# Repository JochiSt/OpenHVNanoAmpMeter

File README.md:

# OpenHVNanoAmpMeter
 Measure Nano Ampere at a high voltage supply

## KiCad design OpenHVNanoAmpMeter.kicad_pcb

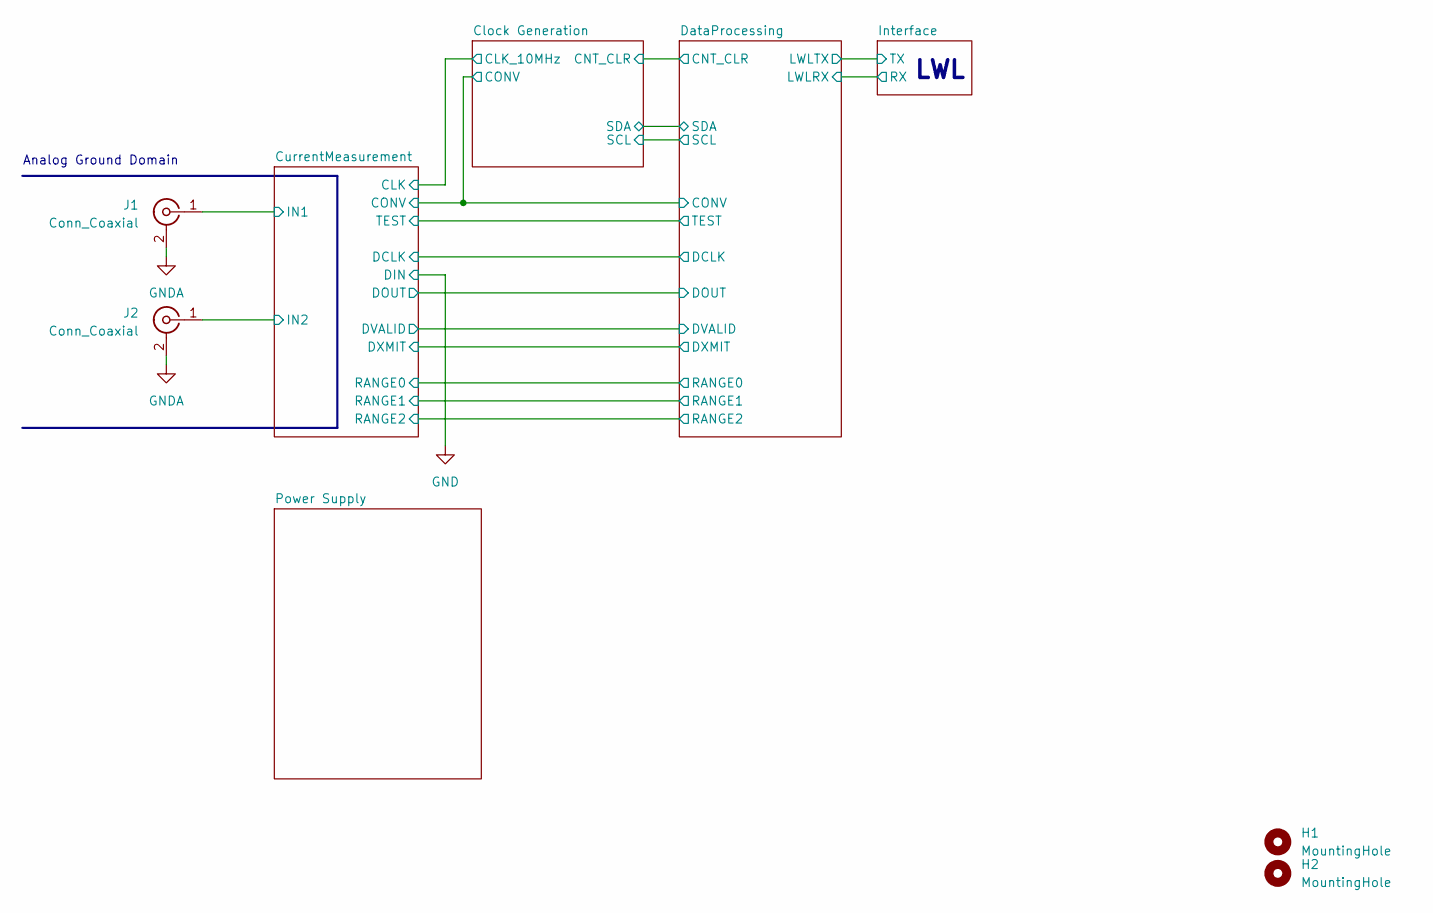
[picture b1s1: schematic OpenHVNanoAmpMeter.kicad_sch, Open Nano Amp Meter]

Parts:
H1, H2: MountingHole; MountingHole_3.2mm_M3_DIN965
J1, J2: Conn_Coaxial; SMA_Amphenol_132289_EdgeMount

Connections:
/CurrentMeasurement/IN1: J1.1 (In); also elsewhere on the board
/CurrentMeasurement/IN2: J2.1 (In); also elsewhere on the board
GNDA: J1.2 (Ext), J2.2 (Ext); also elsewhere on the board

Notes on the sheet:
LWL
Analog Ground Domain

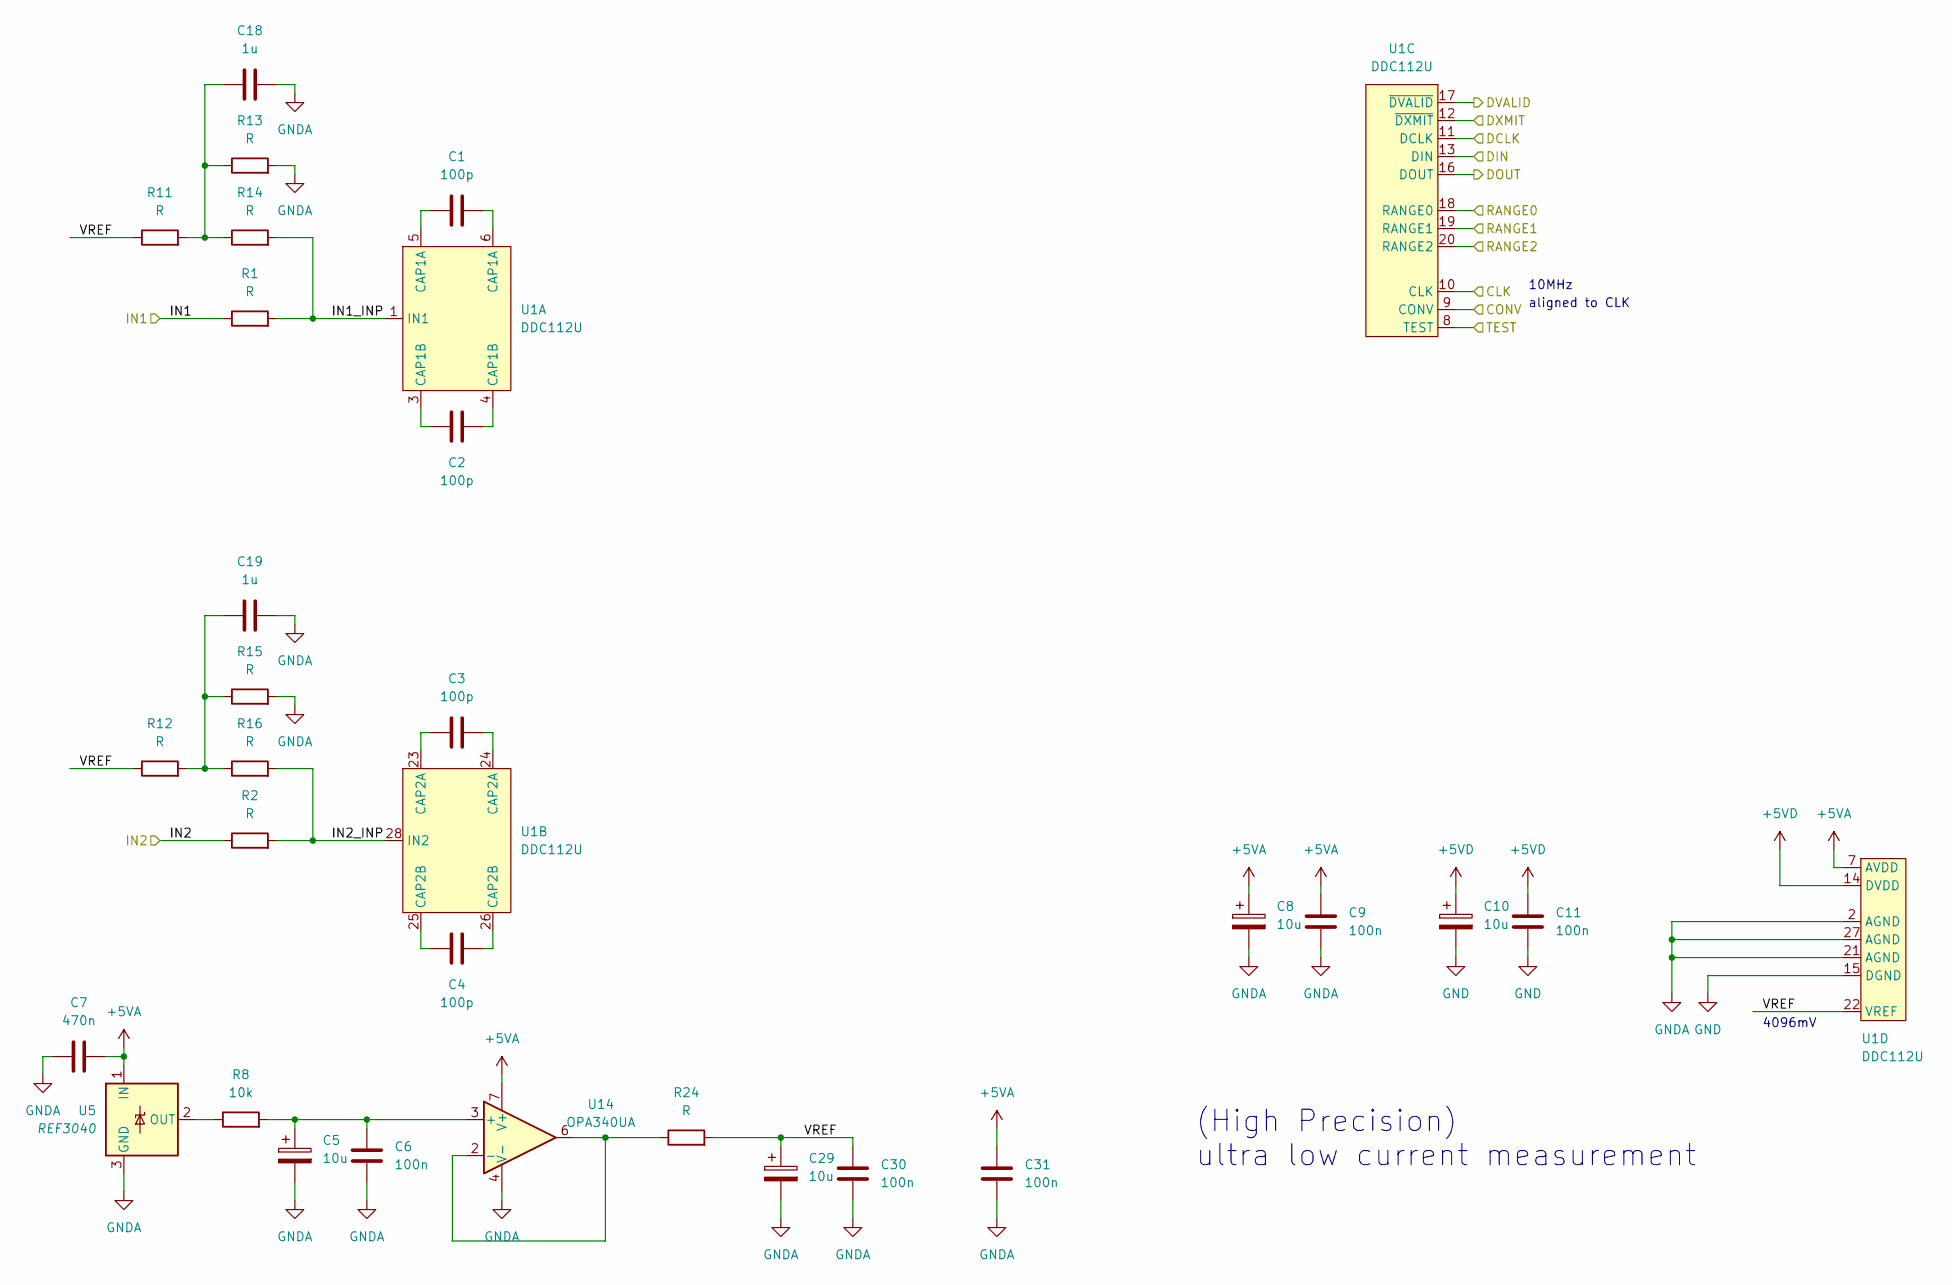
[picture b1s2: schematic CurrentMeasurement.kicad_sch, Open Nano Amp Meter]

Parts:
C1, C2, C3, C4: 100p; C_0402_1005Metric_Pad0.74x0.62mm_HandSolder
C5, C8, C10, C29: 10u; CP_Elec_4x3.9
C6, C9, C11, C30, C31: 100n; C_0603_1608Metric
C7: 470n; C_0603_1608Metric
C18, C19: 1u; C_0603_1608Metric
R1, R2, R11, R12, R13, R14, R15, R16, R24: R; R_0603_1608Metric
R8: 10k; R_0603_1608Metric
U1: DDC112U; SOIC-28W_7.5x17.9mm_P1.27mm
U5: REF3040; SOT-23
U14: OPA340UA; SOIC-8_3.9x4.9mm_P1.27mm

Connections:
+5VA: C7.2, C8.1, C9.1, C31.1, U1.7 (AVDD), U5.1 (IN), U14.7 (V+); also elsewhere on the board
+5VD: C10.1, C11.1, U1.14 (DVDD); also elsewhere on the board
/Clock Generation/CLK_10MHz: U1.10 (CLK); also elsewhere on the board
/Clock Generation/CONV: U1.9 (CONV); also elsewhere on the board
/CurrentMeasurement/DCLK: U1.11 (DCLK); also elsewhere on the board
/CurrentMeasurement/DOUT: U1.16 (DOUT); also elsewhere on the board
/CurrentMeasurement/DVALID: U1.17 (~DVALID); also elsewhere on the board
/CurrentMeasurement/DXMIT: U1.12 (~DXMIT); also elsewhere on the board
/CurrentMeasurement/IN1: R1.1; also elsewhere on the board
/CurrentMeasurement/IN1_INP: R1.2, R14.2, U1.1 (IN1)
/CurrentMeasurement/IN2: R2.1; also elsewhere on the board
/CurrentMeasurement/IN2_INP: R2.2, R16.2, U1.28 (IN2)
/CurrentMeasurement/RANGE0: U1.18 (RANGE0); also elsewhere on the board
/CurrentMeasurement/RANGE1: U1.19 (RANGE1); also elsewhere on the board
/CurrentMeasurement/RANGE2: U1.20 (RANGE2); also elsewhere on the board
/CurrentMeasurement/TEST: U1.8 (TEST); also elsewhere on the board
/CurrentMeasurement/VREF: C29.1, C30.1, R11.1, R12.1, R24.2, U1.22 (VREF)
GND: C10.2, C11.2, U1.13 (DIN), U1.15 (DGND); also elsewhere on the board
GNDA: C5.2, C6.2, C7.1, C8.2, C9.2, C18.2, C19.2, C29.2, C30.2, C31.2, R13.2, R15.2, U1.2 (AGND), U1.21 (AGND), U1.27 (AGND), U5.3 (GND), U14.4 (V-); also elsewhere on the board
unnamed: C1.1, U1.5 (CAP1A)
unnamed: C1.2, U1.6 (CAP1A)
unnamed: C2.1, U1.3 (CAP1B)
unnamed: C2.2, U1.4 (CAP1B)
unnamed: C3.1, U1.23 (CAP2A)
unnamed: C3.2, U1.24 (CAP2A)
unnamed: C4.1, U1.25 (CAP2B)
unnamed: C4.2, U1.26 (CAP2B)
unnamed: C5.1, C6.1, R8.2, U14.3 (+)
unnamed: C18.1, R11.2, R13.1, R14.1
unnamed: C19.1, R12.2, R15.1, R16.1
unnamed: R8.1, U5.2 (OUT)
unnamed: R24.1, U14.2 (-), U14.6

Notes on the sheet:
4096mV
aligned to CLK
(High Precision) ultra low current measurement
10MHz

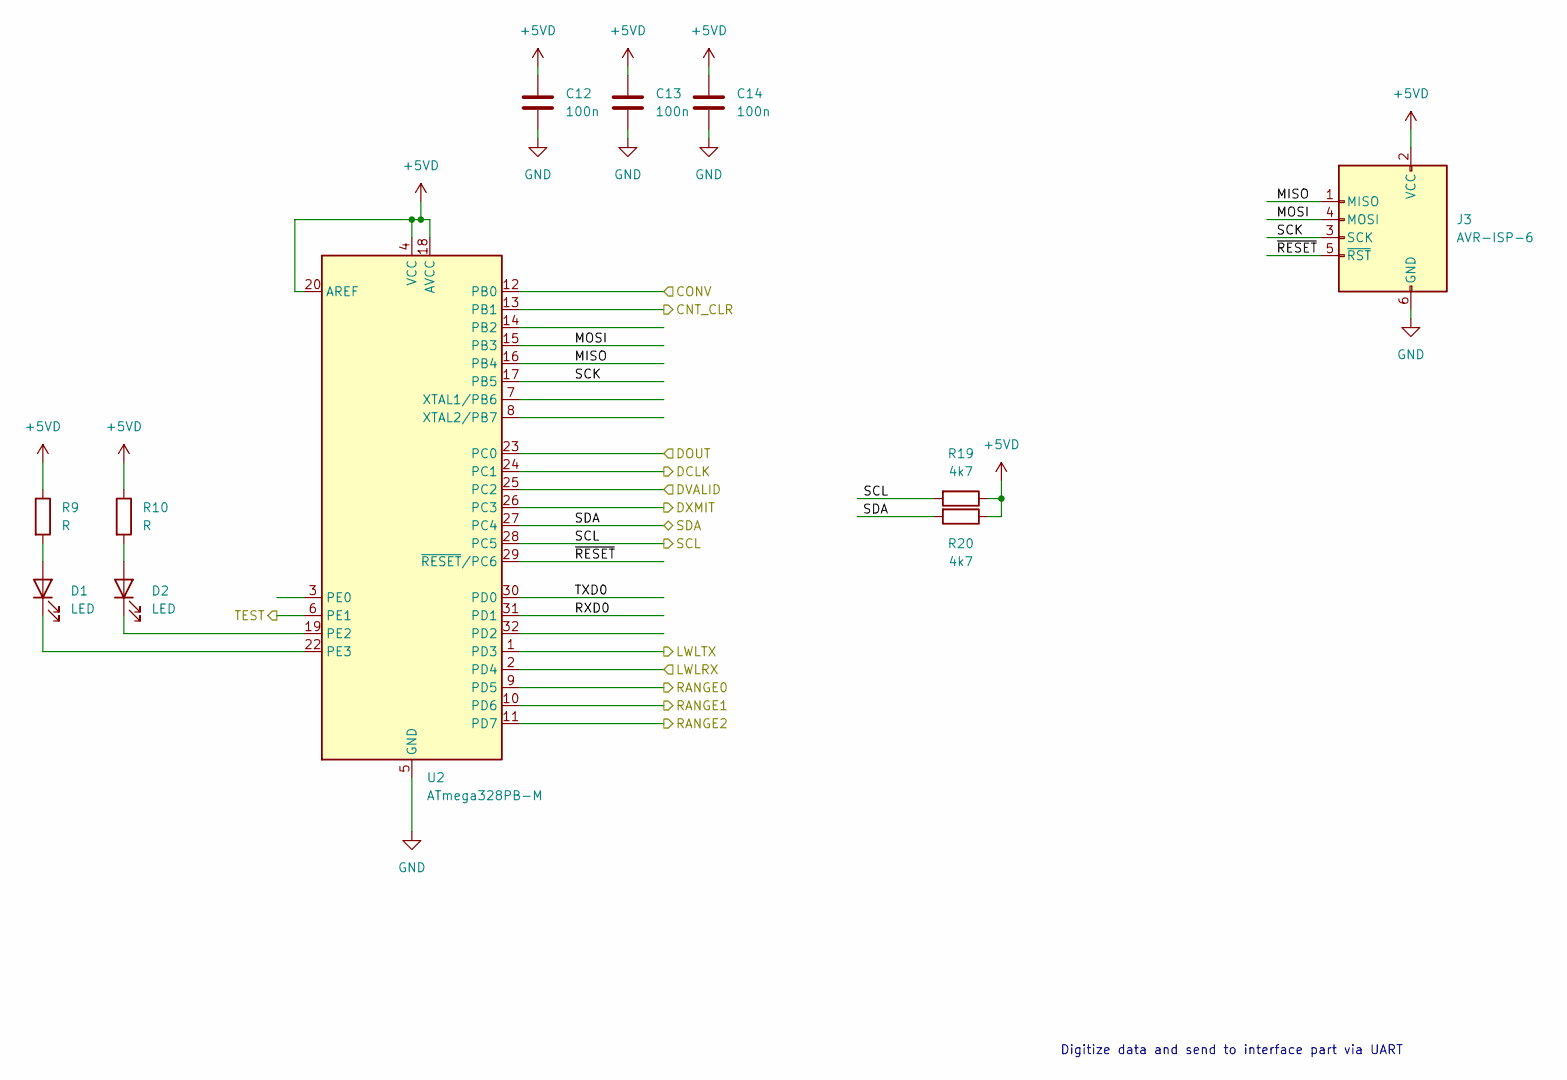
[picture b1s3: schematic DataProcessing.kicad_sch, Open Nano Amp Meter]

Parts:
C12, C13, C14: 100n; C_0603_1608Metric
D1, D2: LED; LED_0603_1608Metric
J3: AVR-ISP-6; PinHeader_2x03_P2.54mm_Vertical_SMD
R9, R10: R; R_0603_1608Metric
R19, R20: 4k7; R_0603_1608Metric
U2: ATmega328PB-M; QFN-32-1EP_5x5mm_P0.5mm_EP3.1x3.1mm

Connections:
+5VD: C12.1, C13.1, C14.1, J3.2 (VCC), R9.1, R10.1, R19.1, R20.1, U2.4 (VCC), U2.18 (AVCC), U2.20 (AREF); also elsewhere on the board
/Clock Generation/CNT_CLR: U2.13 (PB1); also elsewhere on the board
/Clock Generation/CONV: U2.12 (PB0); also elsewhere on the board
/CurrentMeasurement/DCLK: U2.24 (PC1); also elsewhere on the board
/CurrentMeasurement/DOUT: U2.23 (PC0); also elsewhere on the board
/CurrentMeasurement/DVALID: U2.25 (PC2); also elsewhere on the board
/CurrentMeasurement/DXMIT: U2.26 (PC3); also elsewhere on the board
/CurrentMeasurement/RANGE0: U2.9 (PD5); also elsewhere on the board
/CurrentMeasurement/RANGE1: U2.10 (PD6); also elsewhere on the board
/CurrentMeasurement/RANGE2: U2.11 (PD7); also elsewhere on the board
/CurrentMeasurement/TEST: U2.6 (PE1); also elsewhere on the board
/DataProcessing/LWLRX: U2.2 (PD4); also elsewhere on the board
/DataProcessing/LWLTX: U2.1 (PD3); also elsewhere on the board
/DataProcessing/MISO: J3.1 (MISO), U2.16 (PB4)
/DataProcessing/MOSI: J3.4 (MOSI), U2.15 (PB3)
/DataProcessing/RXD0: U2.31 (PD1)
/DataProcessing/SCK: J3.3 (SCK), U2.17 (PB5)
/DataProcessing/SCL: R19.2, U2.28 (PC5); also elsewhere on the board
/DataProcessing/SDA: R20.2, U2.27 (PC4); also elsewhere on the board
/DataProcessing/TXD0: U2.30 (PD0)
/DataProcessing/~RESET: J3.5 (~RST), U2.29 (~RESET/PC6)
GND: C12.2, C13.2, C14.2, J3.6 (GND), U2.5 (GND), U2.21 (GND), U2.33 (GND); also elsewhere on the board
unnamed: D1.1 (K), U2.22 (PE3)
unnamed: D1.2 (A), R9.2
unnamed: D2.1 (K), U2.19 (PE2)
unnamed: D2.2 (A), R10.2

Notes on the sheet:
Digitize data and send to interface part via UART

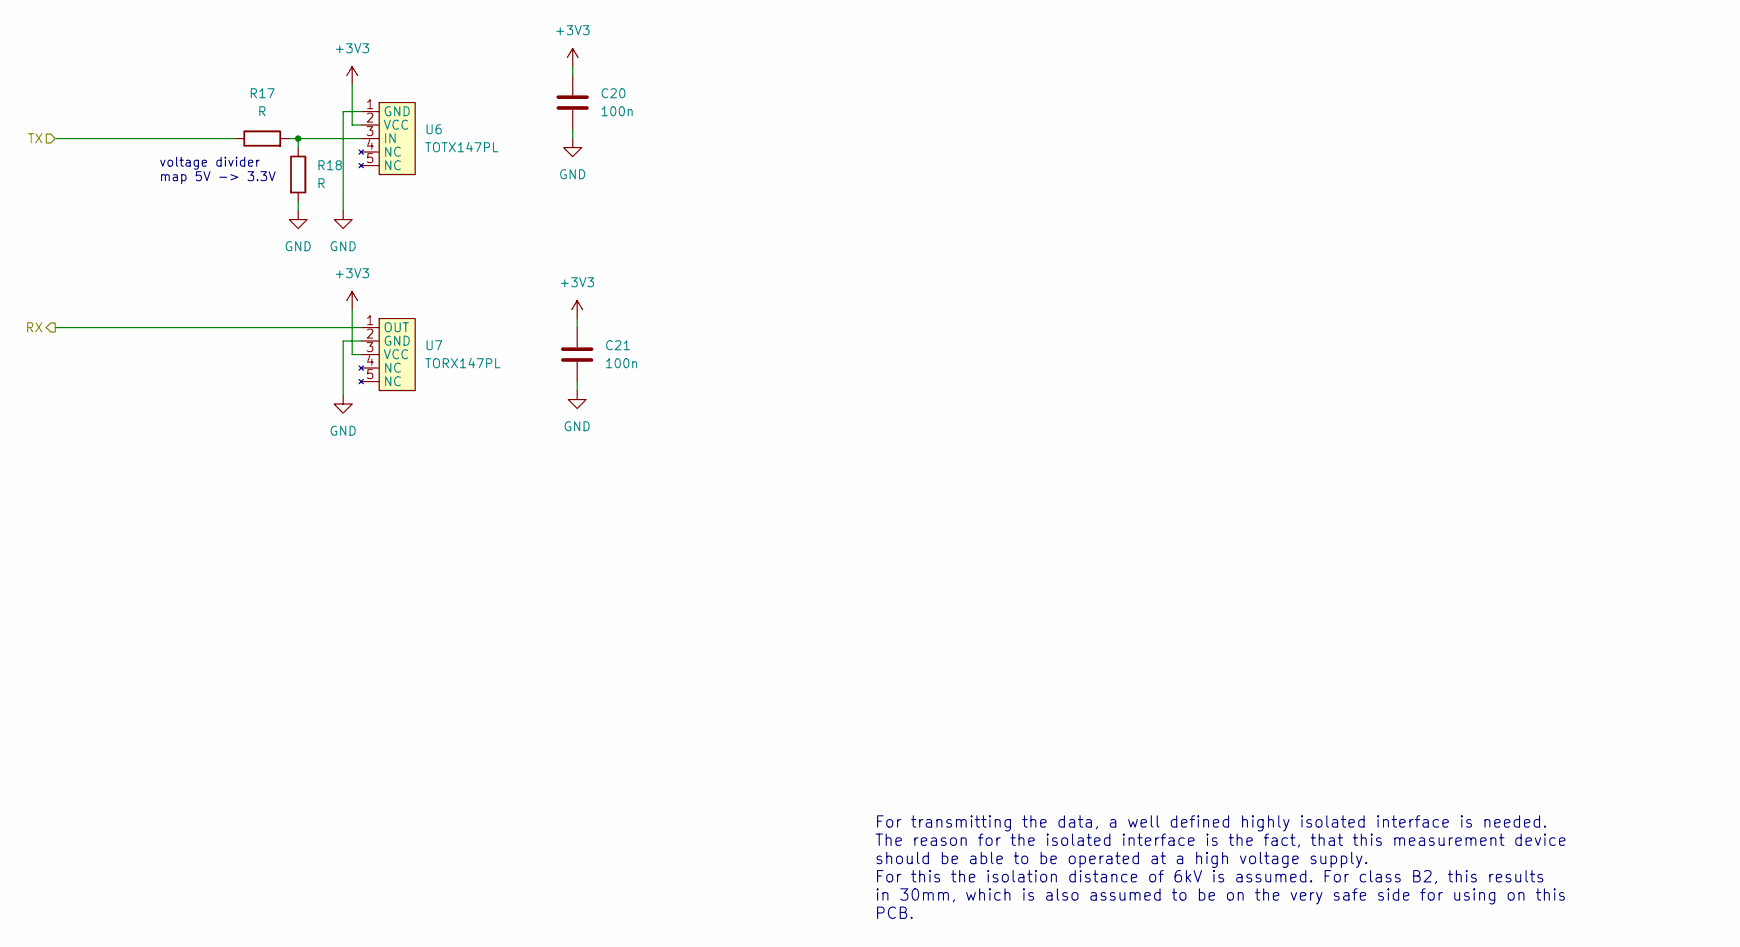
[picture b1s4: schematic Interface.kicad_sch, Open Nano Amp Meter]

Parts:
C20, C21: 100n; C_0603_1608Metric
R17, R18: R; R_0603_1608Metric
U6: TOTX147PL
U7: TORX147PL

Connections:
+3V3: C20.1, C21.1, U6.2 (VCC), U7.3 (VCC); also elsewhere on the board
/DataProcessing/LWLRX: U7.1 (OUT); also elsewhere on the board
/DataProcessing/LWLTX: R17.1; also elsewhere on the board
GND: C20.2, C21.2, R18.2, U6.1 (GND), U7.2 (GND); also elsewhere on the board
unnamed: R17.2, R18.1, U6.3 (IN)

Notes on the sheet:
voltage divider map 5V -> 3.3V
For transmitting the data, a well defined highly isolated interface is needed. The reason for the isolated interface is the fact, that this measurement device should be able to be operated at a high voltage supply. For this the isolation distance of 6kV is assumed. For class B2, this results in 30m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

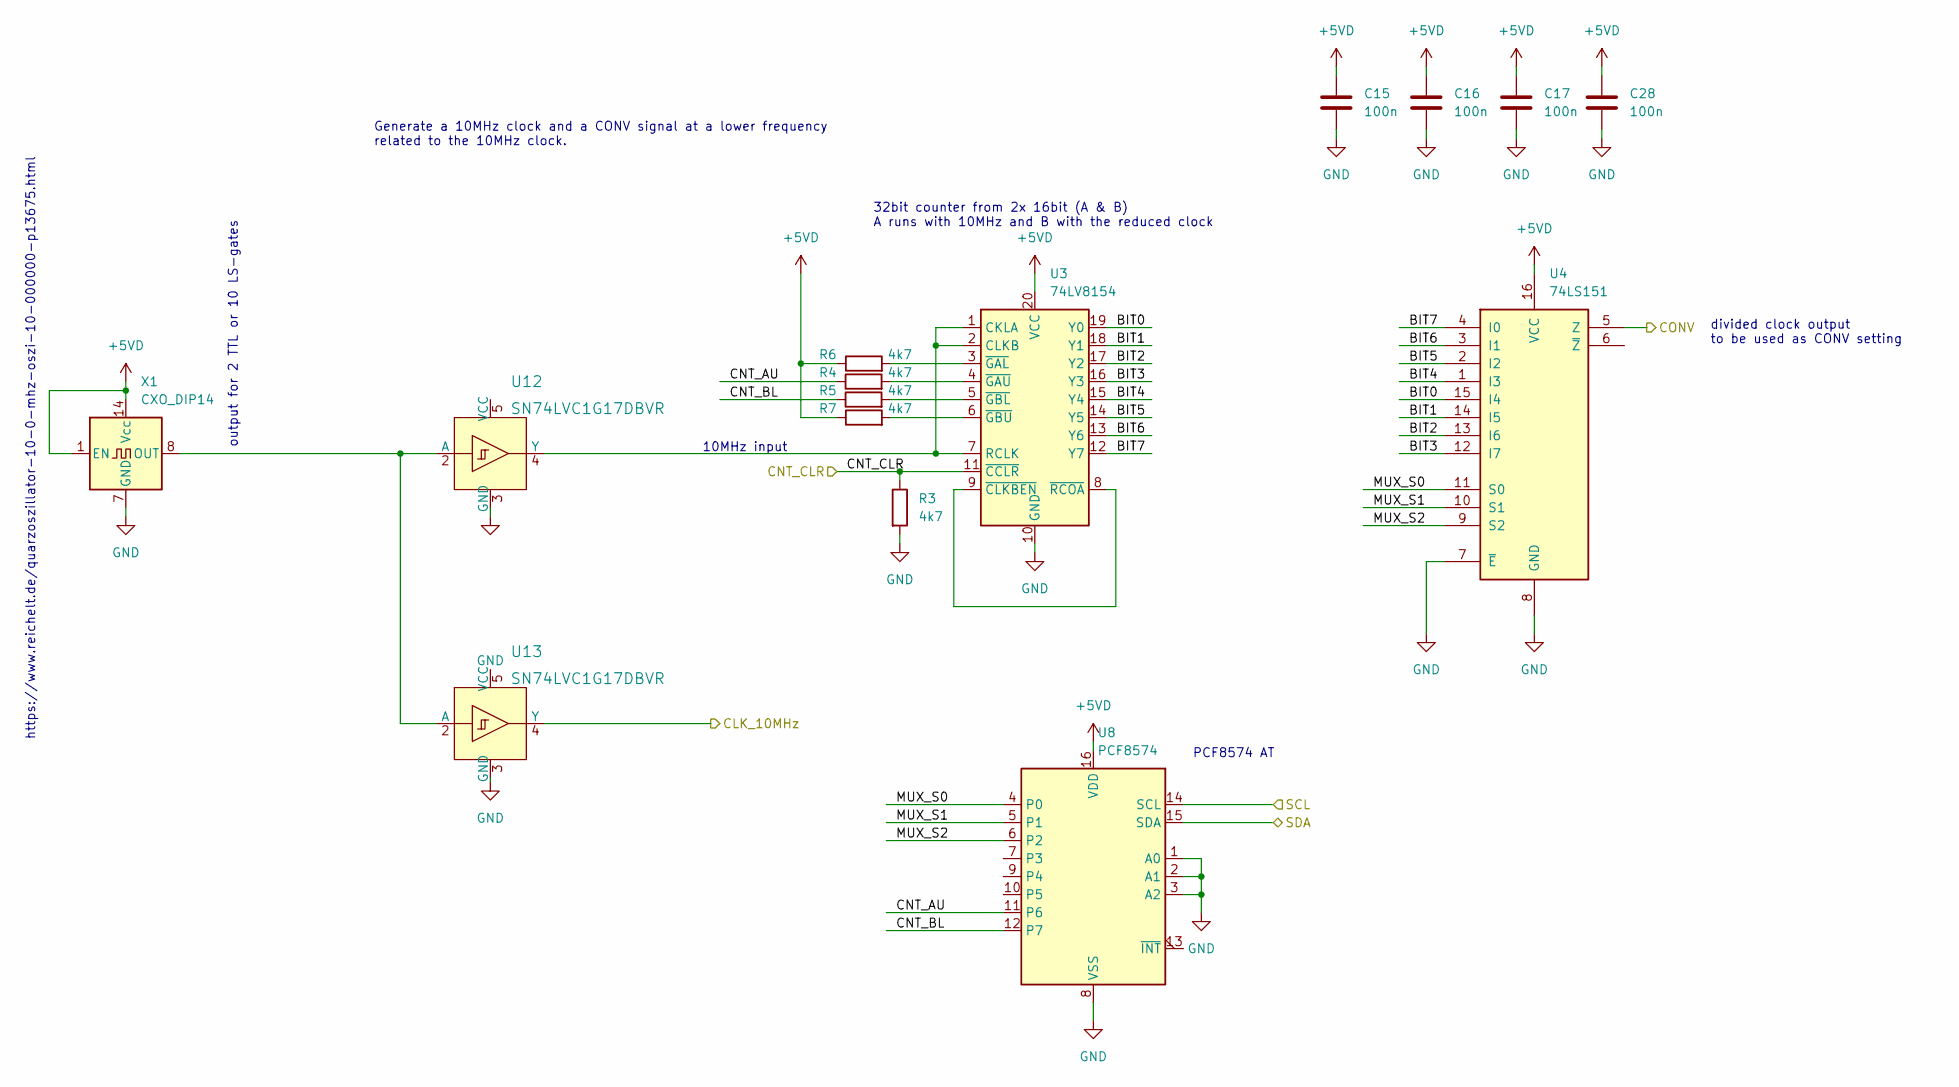
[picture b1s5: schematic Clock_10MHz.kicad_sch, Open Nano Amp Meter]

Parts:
C15, C16, C17, C28: 100n; C_0603_1608Metric
R3: 4k7; R_0603_1608Metric
R4, R5, R6, R7: 4k7; R_0402_1005Metric
U3: 74LV8154; TSSOP-20_4.4x6.5mm_P0.65mm
U4: 74LS151; SO-16_3.9x9.9mm_P1.27mm
U8: PCF8574; SOIC-16W_7.5x10.3mm_P1.27mm
U12, U13: SN74LVC1G17DBVR; SOT-753; MPN SN74LVC1G17DBVR; Digi-Key_PN 296-11933-1-ND
X1: CXO_DIP14; Oscillator_DIP-14

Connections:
+5VD: C15.1, C16.1, C17.1, C28.1, R6.1, R7.1, U3.20 (VCC), U4.16 (VCC), U8.16 (VDD), X1.1 (EN), X1.14 (Vcc); also elsewhere on the board
/Clock Generation/BIT0: U3.19 (Y0), U4.15 (I4)
/Clock Generation/BIT1: U3.18 (Y1), U4.14 (I5)
/Clock Generation/BIT2: U3.17 (Y2), U4.13 (I6)
/Clock Generation/BIT3: U3.16 (Y3), U4.12 (I7)
/Clock Generation/BIT4: U3.15 (Y4), U4.1 (I3)
/Clock Generation/BIT5: U3.14 (Y5), U4.2 (I2)
/Clock Generation/BIT6: U3.13 (Y6), U4.3 (I1)
/Clock Generation/BIT7: U3.12 (Y7), U4.4 (I0)
/Clock Generation/CLK_10MHz: U13.4 (Y); also elsewhere on the board
/Clock Generation/CNT_AU: R4.1, U8.11 (P6)
/Clock Generation/CNT_BL: R5.1, U8.12 (P7)
/Clock Generation/CNT_CLR: R3.1, U3.11 (~CCLR); also elsewhere on the board
/Clock Generation/CONV: U4.5 (Z); also elsewhere on the board
/Clock Generation/MUX_S0: U4.11 (S0), U8.4 (P0)
/Clock Generation/MUX_S1: U4.10 (S1), U8.5 (P1)
/Clock Generation/MUX_S2: U4.9 (S2), U8.6 (P2)
/DataProcessing/SCL: U8.14 (SCL); also elsewhere on the board
/DataProcessing/SDA: U8.15 (SDA); also elsewhere on the board
GND: C15.2, C16.2, C17.2, C28.2, R3.2, U3.10 (GND), U4.7 (~E), U4.8 (GND), U8.1 (A0), U8.2 (A1), U8.3 (A2), U8.8 (VSS), U12.3 (GND), U13.3 (GND), X1.7 (GND); also elsewhere on the board
unnamed: R4.2, U3.4 (~GAU)
unnamed: R5.2, U3.5 (~GBL)
unnamed: R6.2, U3.3 (~GAL)
unnamed: R7.2, U3.6 (~GBU)
unnamed: U3.8 (~RCOA), U3.9 (~CLKBEN)
unnamed: U12.2 (A), U13.2 (A), X1.8 (OUT)
unnamed: U3.1 (CKLA), U3.2 (CLKB), U3.7 (RCLK), U12.4 (Y)

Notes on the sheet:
https://www.reichelt.de/quarzoszillator-10-0-mhz-oszi-10-000000-p13675.html
32bit counter from 2x 16bit (A & B) A runs with 10MHz and B with the reduced clock
output for 2 TTL or 10 LS-gates
Generate a 10MHz clock and a CONV signal at a lower frequency related to the 10MHz clock.
10MHz input
divided clock output to be used as CONV setting
PCF8574 AT

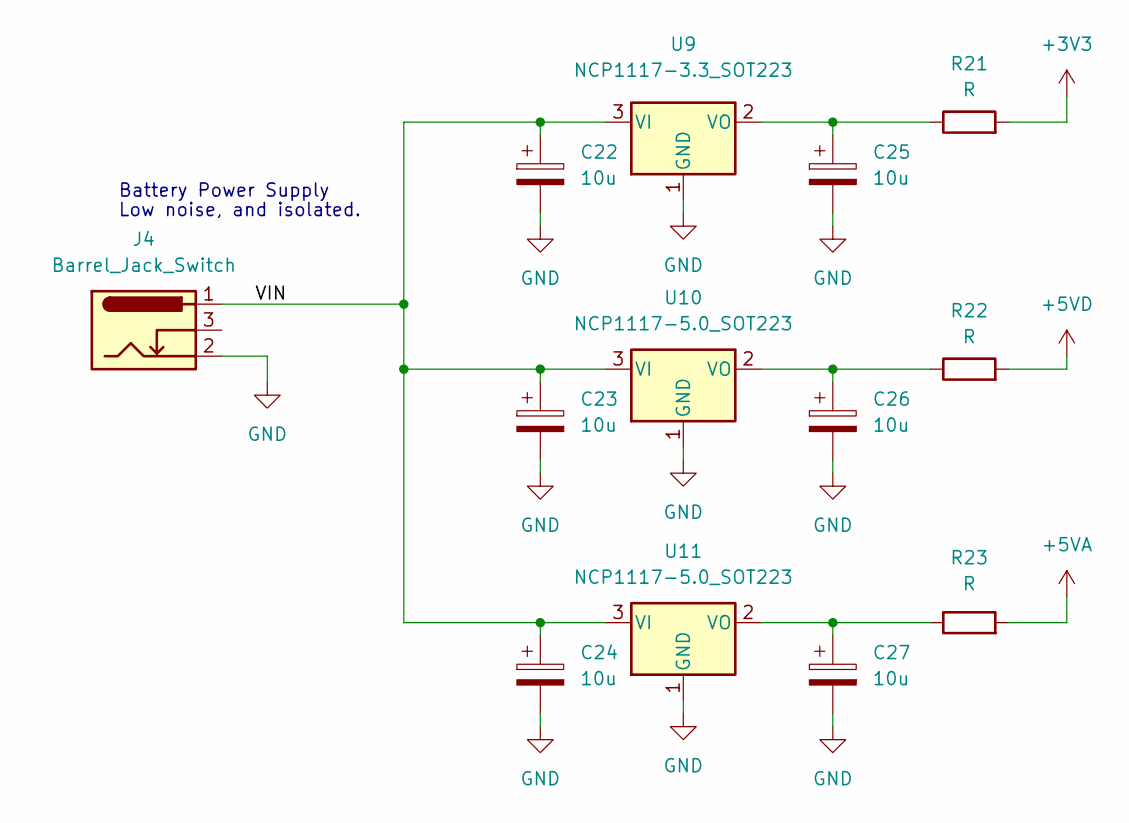
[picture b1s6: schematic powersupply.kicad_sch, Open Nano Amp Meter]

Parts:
C22, C23, C24, C25, C26, C27: 10u; CP_Elec_4x3.9
J4: Barrel_Jack_Switch; BarrelJack_Wuerth_6941xx301002
R21, R22, R23: R; R_0603_1608Metric
U9: NCP1117-3.3_SOT223; SOT-223-3_TabPin2
U10, U11: NCP1117-5.0_SOT223; SOT-223-3_TabPin2

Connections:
+3V3: R21.2; also elsewhere on the board
+5VA: R23.2; also elsewhere on the board
+5VD: R22.2; also elsewhere on the board
/Power Supply/VIN: C22.1, C23.1, C24.1, J4.1, U9.3 (VI), U10.3 (VI), U11.3 (VI)
GND: C22.2, C23.2, C24.2, C25.2, C26.2, C27.2, J4.2, U9.1 (GND), U10.1 (GND), U11.1 (GND); also elsewhere on the board
unnamed: C25.1, R21.1, U9.2 (VO)
unnamed: C26.1, R22.1, U10.2 (VO)
unnamed: C27.1, R23.1, U11.2 (VO)

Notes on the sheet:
Battery Power Supply
Low noise, and isolated.

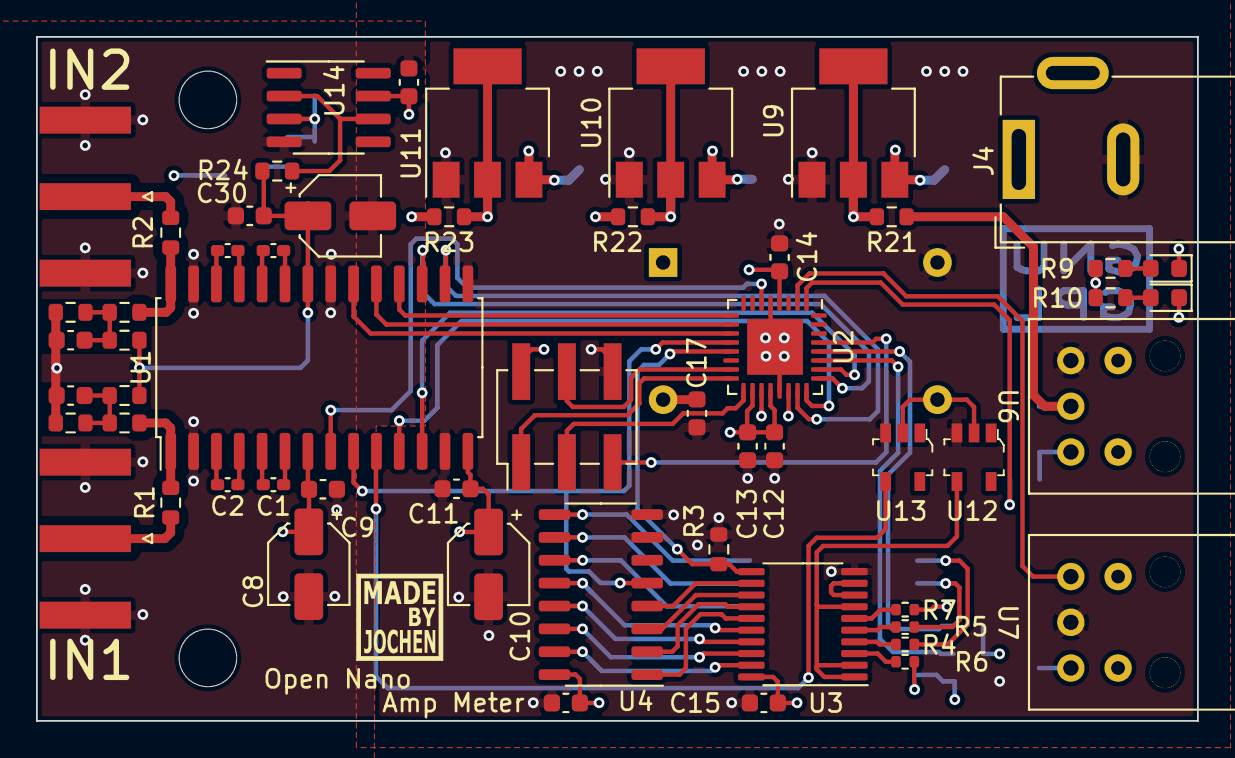
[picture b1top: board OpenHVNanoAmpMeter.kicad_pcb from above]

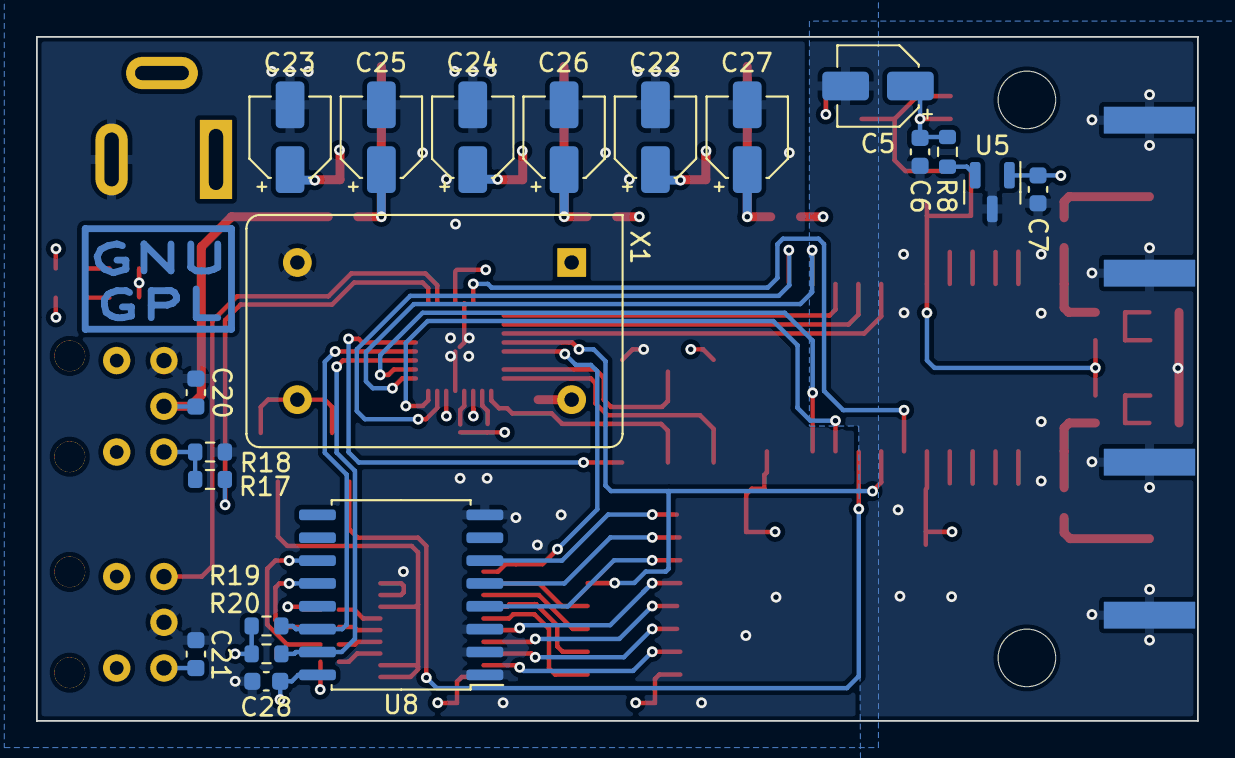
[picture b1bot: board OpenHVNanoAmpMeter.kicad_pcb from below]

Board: 4 copper layers, 64.5 x 38.0 mm, 78 parts (20 on the bottom side), 71 nets.

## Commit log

2022-10-26 added rough project structure
2022-10-27 added README how to get the TLC272 library
2022-10-27 ignore the files downloaded from TI
2022-10-27 added simulation for current measurement
2022-10-27 ignore simulation output
2022-10-27 added some explanations
2022-10-27 added plot settings for the simulation
2022-10-27 added low pass filtering
    this reduces the bandwidth, but for stady state current measurements, this might increase the stability and reduces the noise impact. On the other hand, this needs proper tuning, because the filterin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
2022-10-27 added a link to one TLC272 example circuit
2022-10-27 added a bit more structure
    by grouping the components and adding some more labels
2022-10-27 fixed 2nd stage amplification
2022-10-27 added more current output channels
    for getting more ranges
2022-10-27 added TIA schematic
    started with TLC272
2022-10-27 updated structure
2022-11-15 added library for the DDC112
2022-11-15 changed from TIA to DDC112, because this might be the simpler approach
2022-11-15 added a comment to the interface about constrains
2022-11-15 added hierachical ports to sheet
2022-11-15 started layout with DDC112
2022-11-15 small project update
2022-11-15 added ports for interface section
2022-11-16 ignore auto saved file list
2022-11-16 ignore spyder folder
2022-11-16 added some comments
2022-11-16 added script for DDC112 parameter estimation
    script calculates valid clock divider settings and the full scale current
2022-11-16 added 10 MHz and CONV generation
    using a counter and a MUX various integration times are possible
2022-11-16 started dataprocessing
    using a Atmega328PB
2022-11-16 removed level shifter
2022-11-16 added coax connectors as input
2022-11-16 included input resistors
2022-11-16 started some layouting
2022-11-16 change to \textmu
2022-11-16 use proper capacitance value
2022-11-16 use uA for displaying the fullscale current
2022-11-16 changed formatting of label (increased digits)
2022-11-16 use 2nd X axis to display the clock divider setting
2022-11-16 adjusted image size and removed commented out part of code
2022-11-16 added 2nd y axis for LSB size
    include the calculation of the LSB size to give a hint towards the sensitivity of the system
2022-11-16 plot legend as the very last step
    so it is above all other items
2022-11-16 fixed y axis label
    and added comment about calculation of axis ticks
2022-11-16 remove debug print
2022-11-16 added two lines to guide the eye
    one at 1 uA and the other one at 1 nA
2022-11-16 connected the ICs to 5V digital power
2022-11-17 power annotation
2022-11-17 added decoupling Cs
2022-11-17 added decoupling Cs + reference voltage generation
    for reference voltage generation, the buffer OPamp is missing
2022-11-17 small project updates
2022-11-17 proceeded with routing
2022-11-17 ISP connection routed
2022-11-17 changed title block to meaningful information
2022-11-17 enumeration done
2022-11-17 added 2 LEDs for some status output
2022-11-18 correct for zero code of DDC112
2022-11-18 updated 2nd yaxis title
    we no longer have the full 20 bit FS, because the zero code is accounted for
2022-11-18 added option to make the input bipolar
2022-11-18 changed resistor footprint to 0603
2022-11-18 added simulation folder for Manchester Encoding
2022-11-18 added GitHub Gist for generating a UART PWL file
2022-11-18 added a LTspice simulation of Hardware Manchester Encoding
2022-11-23 added TOSLINK TO?X147PL footprints
2022-11-23 added symbols for TOSLINK TO?X147PL
2022-11-23 updated title block
2022-11-23 added TOSLINK RX & TX
2022-11-23 changed setting of clock divider to I2C
    reduces pin load on uC, thus frees pins for usage with other functions.
2022-11-23 added labels to input sections
2022-11-23 include TO?X147 in symbol table
2022-11-24 added 3 linear regulators
2022-11-24 added mounting holes and renamed TX & RX to LWL*
2022-11-24 added 100nF decoupling and global 3V3 net
2022-11-24 implemented I2C incl. pullups
2022-11-24 implemented linear regulators
2022-11-24 added 0.5mm width constrain
2022-11-24 updated 10MHz oscillator to DIP 14 package
    needs larger PCB space, but much easier to purchase
2022-11-24 inlcuded buffer for 10MHz clock
    otherwise the oscillator does not have enough drive strength
2022-11-24 added buffer to ref voltage generation
2022-11-24 added note to PCF8574
2022-11-24 added MadeByJochen + GPL symbol
2022-11-24 small tidy up of traces
2022-11-24 layout partially done
    almost final routing (needs many checks and tests)
2022-11-25 DRC clean layout (incl. exclusion of violations)
2022-12-31 added plot integration time vs. full scale current
